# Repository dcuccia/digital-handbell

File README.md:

# Digital Handbell

**A real ringing gesture. A digitally voiced bell. An open design to build together.**

We're developing a rechargeable, motion-triggered musical instrument with a
local speaker, custom electronics, and a removable cartridge inside a
3D-printed bell. The goal is expressive, affordable music-making without a
phone or computer during play.

[Project site and 3D board](https://dcuccia.github.io/digital-handbell/) ·
[Build a handbell](docs/build-a-handbell.md) ·
[Explore the design](docs/design-gallery.md) ·
[Roadmap](docs/roadmap.md) ·
[Join the project](CONTRIBUTING.md) ·
[Documentation](docs/README.md)

*Enclosure concept, not a product photograph. These preserved CAD views
predate the latest six-layer PCB; fitting that board and its speaker
connector into the assembly is still on the roadmap.*

## Where we are

**November 2026: the six-layer PCB has reached zero unconnected items, and
the first prototype PCBA batch has been ordered.** The next step is turning
those boards into a reviewed, working instrument.

| Ready to explore | Still to do |
|---|---|
| Native KiCad schematic, routed PCB and local libraries | Electrical/DFM review and disposition of remaining rule findings |
| FreeCAD enclosure/cartridge studies and inert fit-print files | Updated assembly for the six-layer board, connector/harness clearance and physical fit |
| Prototype PCBA order placed with JLCPCB (quoted as 10 PCBs, 8 assembled) | Incoming inspection: confirm substitutions, via fill, placements and polarity on arrival, then staged bring-up |
| Firmware, audio and gesture requirements | Implement and demonstrate a sounding instrument; measure latency, noise and runtime |

This is **an engineering prototype, not a build-ready kit**. Ordering
first articles is how we find out what works; it is not a fabrication
release or safety approval. Zero opens means the connectivity check found
no unconnected items; it does not prove the circuit works. The public
snapshot retains 291 non-open DRC findings
and 46 schematic-parity findings. Electrical, mechanical, manufacturing
and safety review remain open. No child-use qualification is claimed.

[Board review and remaining risks](docs/pcb-review-2026-11.md) ·
[Order package](hardware/handbell/quote-prep/2026-11-09-six-layer/README.md) ·
[Incoming checks](hardware/handbell/quote-prep/2026-11-09-six-layer/unresolved-before-ordering.md)

## Inside the design

| Subsystem | Current direction |
|---|---|
| Processing | RP2040 with 2 MB QSPI flash; CircuitPython is the planned firmware path |
| Motion | LSM6DSOX six-axis accelerometer/gyroscope for ringing and damping experiments |
| Sound | MAX98357A I2S amplifier, TPS61023 boosted audio rail and a 40 mm speaker |
| Power and service | Rechargeable 1S Li-ion design, cell protection, USB-C charging/programming and debug access |
| Electronics | Six copper layers; 83 fitted parts: 81 front-side electronic parts and two rear battery contacts |
| Enclosure | Original printed shell, black handle and removable speaker/PCB/cell cartridge |

The intended behavior is local and offline: recognize a ringing gesture,
play a bell sound, and stay quiet between notes. Natural damping,
velocity response, note selection and reliable gesture detection are
development goals, not demonstrated features. Wireless is a future option,
not a dependency of the first instrument.

### The ordered PCBA

| Front: electronics | Back: battery clips |
|:---:|:---:|
|  |  |

*KiCad renders of public snapshot `2f738ccb`, not photographs. Package
models and disclosed stand-ins are used; the battery clips and J1 speaker
connector are simplified project proxies. This is not a fit check.*
**[Rotate it in 3D on the project site](https://dcuccia.github.io/digital-handbell/)** ·
[Build a handbell](docs/build-a-handbell.md) ·
[More views](docs/design-gallery.md)

## Explore without getting lost

| I want to... | Start here |
|---|---|
| See the bell and board | [Design gallery](docs/design-gallery.md) or the [3D project site](https://dcuccia.github.io/digital-handbell/) |
| Build one: parts, printing, harness, assembly | [Build a handbell](docs/build-a-handbell.md) |
| Open the latest electronics | [Six-layer review snapshot](hardware/handbell/iterations/printed-bell-six-layer-review/README.md) |
| Open the enclosure or find STEP/STL files | [Mechanical asset guide](mechanical/README.md) |
| Understand what is next | [Roadmap](docs/roadmap.md) |
| Help with a specific part | [Contributing](CONTRIBUTING.md) |
| Understand the circuits and intended behavior | [Architecture](docs/architecture.md) and [firmware/audio plan](docs/firmware-and-audio.md) |
| Find older experiments or engineering evidence | [Documentation index](docs/README.md) and [hardware revision guide](hardware/handbell/iterations/README.md) |

Keep the whole checkout when opening CAD: some library paths reference
sibling directories. KiCad 10.0.6 and FreeCAD 1.1.3 have been exercised.
No CAD installation is needed to browse the gallery or plans.

## Come build with us

There is useful work for software developers, electronics reviewers,
mechanical designers, musicians and curious first-time contributors.
Near-term needs include CircuitPython/audio experiments, motion replay
tools, PCB review, the updated cartridge fit, and clear assembly/test
documentation. You do not need to route a PCB to help.

Pick a workstream in the [contribution guide](CONTRIBUTING.md), or introduce
your idea in an [issue](https://github.com/dcuccia/digital-handbell/issues).
We track work in the [project board](https://github.com/users/dcuccia/projects/1)
and keep decisions and evidence in the repository.

## Open design, with attribution

The electronics adapt published Adafruit designs, including the RP2040
Prop-Maker Feather, LSM6DSOX breakout and TPS61023 MiniBoost. Original
software, documentation and mechanical work use MIT; adapted hardware
retains **CC BY-SA 3.0**. Mixed CAD exports and images retain their
electronics attribution. See [ATTRIBUTION.md](ATTRIBUTION.md) for the
per-asset boundaries; this is not an Adafruit-endorsed product.

The [2023 design notes](Design%20Notes.md) and
[system diagram](System%20Diagram.pptx) remain preserved. The
[research and routing history](docs/README.md#history-and-research)
records how we reached the current design without making every experiment
the starting point for a new contributor.

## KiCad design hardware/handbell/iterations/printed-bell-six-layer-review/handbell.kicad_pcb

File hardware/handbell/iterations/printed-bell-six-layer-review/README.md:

# Printed-bell six-layer zero-open review snapshot

**Current public electronics review target, November 2026.** This is a
provenance-cleared snapshot, not a fabrication, CAD-fit, functional, safety
or child-use release. The older 37-open four-layer board is preserved
separately; do not use it as the current quote source.

[Project home](../../../../README.md) ·
[Review and risks](../../../../docs/pcb-review-2026-11.md) ·
[Gallery](../../../../docs/design-gallery.md) ·
[Revision guide](../README.md)

## Open and inspect

| Artifact | Purpose |
|---|---|
| [handbell.kicad_pro](handbell.kicad_pro) | Open this project in KiCad 10.0.6; retain the whole checkout for libraries |
| [handbell.kicad_sch](handbell.kicad_sch) | Native schematic with embedded symbols |
| [handbell.kicad_pcb](handbell.kicad_pcb) | Six-layer board `2f738ccb`; 104 footprints, 83 fitted parts |
| [MANIFEST.sha256](MANIFEST.sha256) | Packaged source hashes |
| [Native DRC](reports/native-drc.json) | Zero opens, 291 non-open findings, 46 parity findings; not a clean-board claim |
| [Publication validation](reports/publication-validation.json) | Exact source/delta, library and publication checks |
| [Quote package](../../quote-prep/2026-11-09-six-layer/README.md) | Matching BOM/CPL, quote history and remaining order gates |

The [most recent completed mechanical assembly](../../../../mechanical/README.md)
still binds an older board. There is no six-layer fit-qualified assembly
or populated STEP here.

## Source and provenance

The PCB is a publication derivative of private routing milestone
`0051b2e32c78533f102f3e20cb1bdac3c23377ec9d53b594b4ae5deda663a6bd`.
Only J1's footprint expression was replaced. Its copper lands are independently
derived from the JST ACHL dimensional drawing and retain the accepted pose,
pad numbers, nets, and copper geometry. All non-J1 native objects and saved
fills are preserved by exact-complement proof.

The source project retains the harmless historical internal
`meta.filename = routed-c1.kicad_pro`. The schematic is self-contained for
review, but blanket “Update Footprints from Library” is unsupported for three
legacy schematic alias names; do not use that command as a review step.

See `reports/publication-validation.json` for hashes, geometry, DRC results,
dependency checks, privacy checks, and limits.

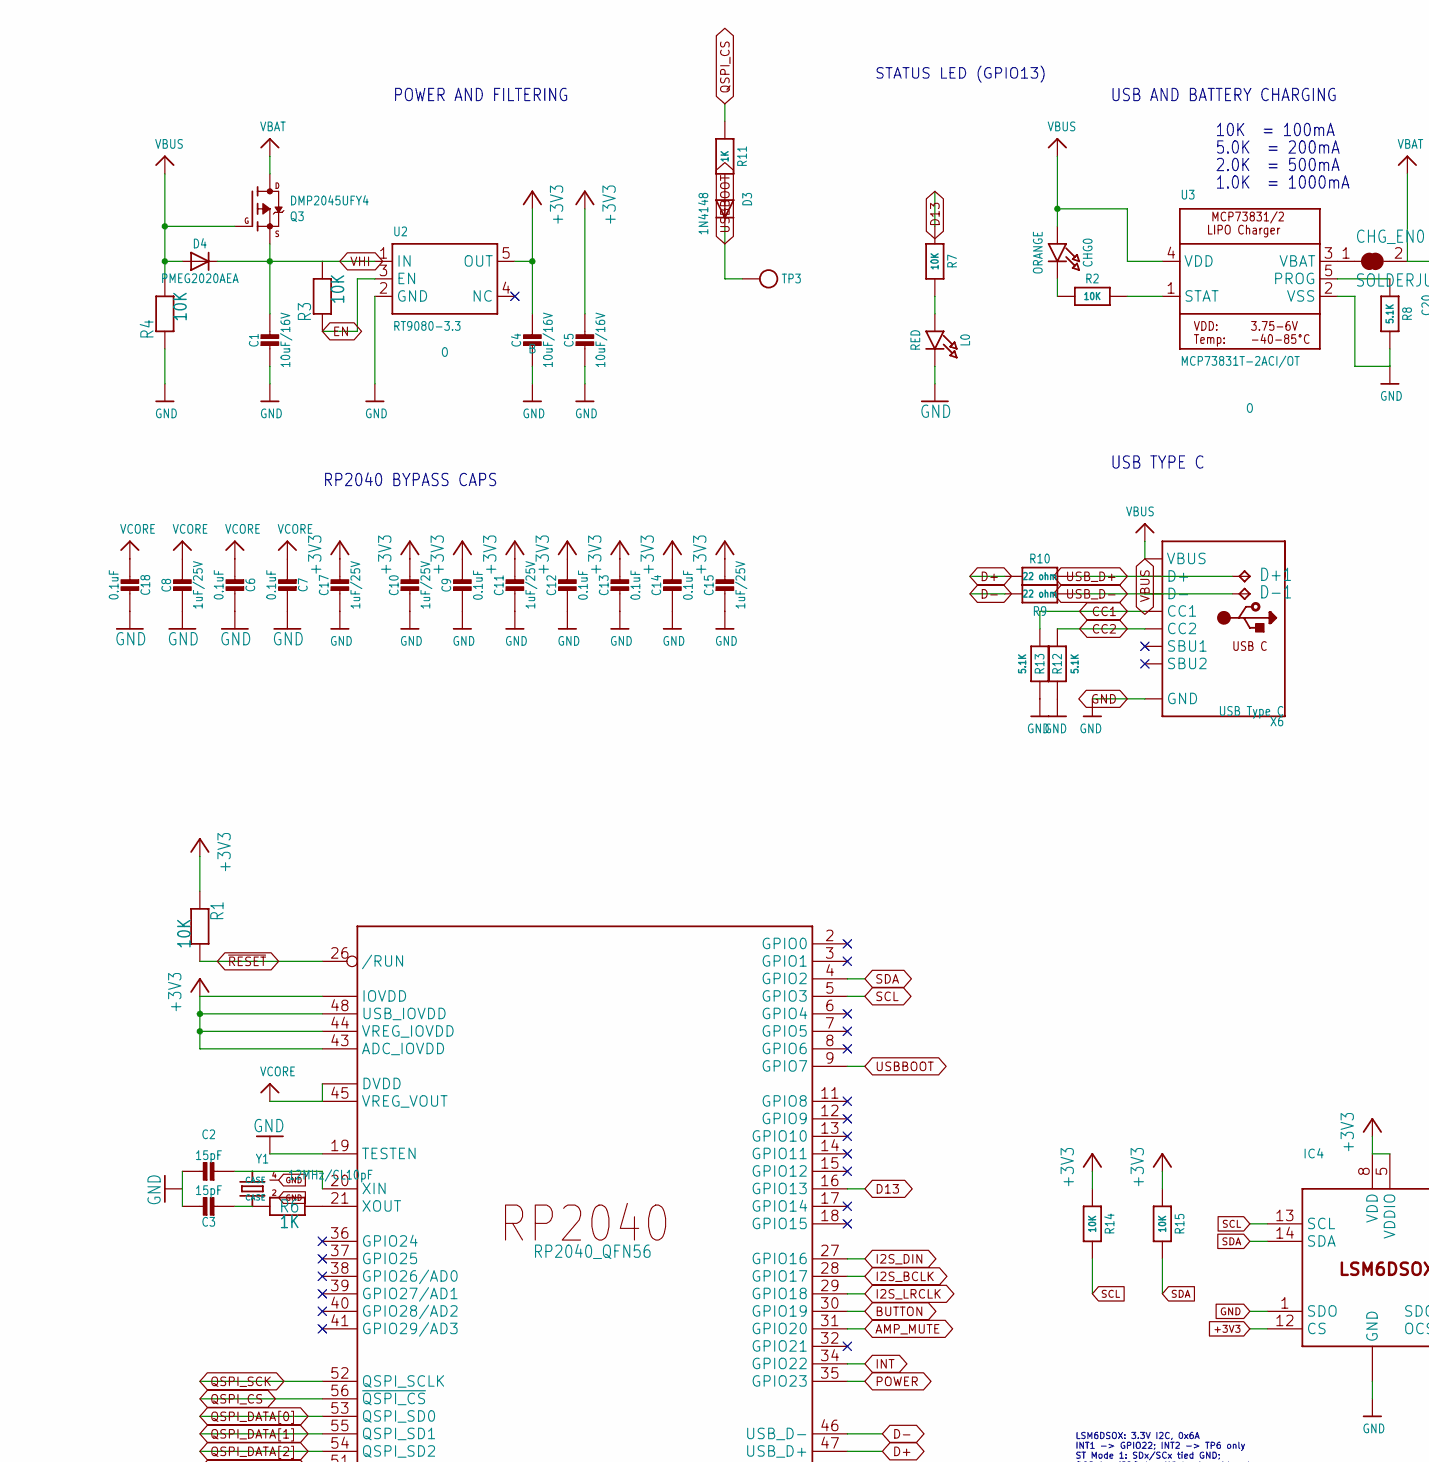
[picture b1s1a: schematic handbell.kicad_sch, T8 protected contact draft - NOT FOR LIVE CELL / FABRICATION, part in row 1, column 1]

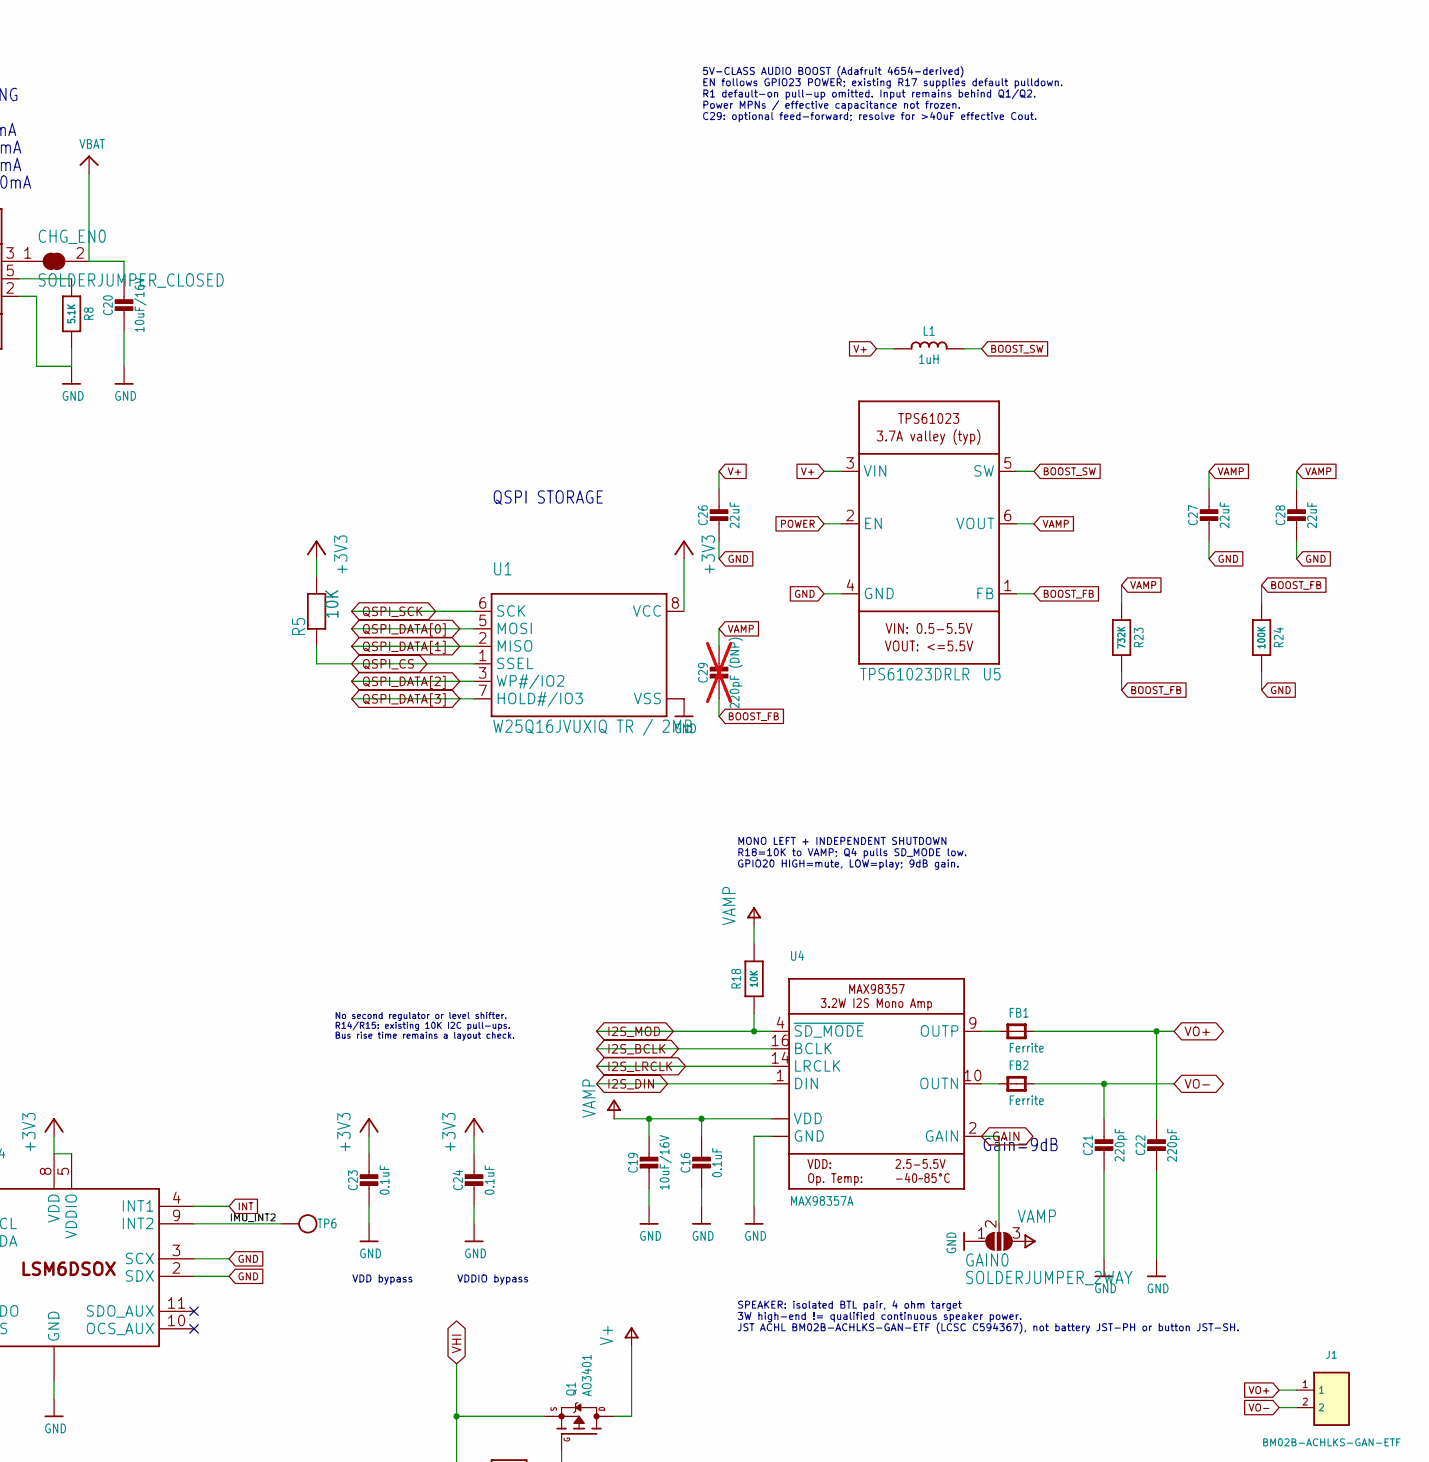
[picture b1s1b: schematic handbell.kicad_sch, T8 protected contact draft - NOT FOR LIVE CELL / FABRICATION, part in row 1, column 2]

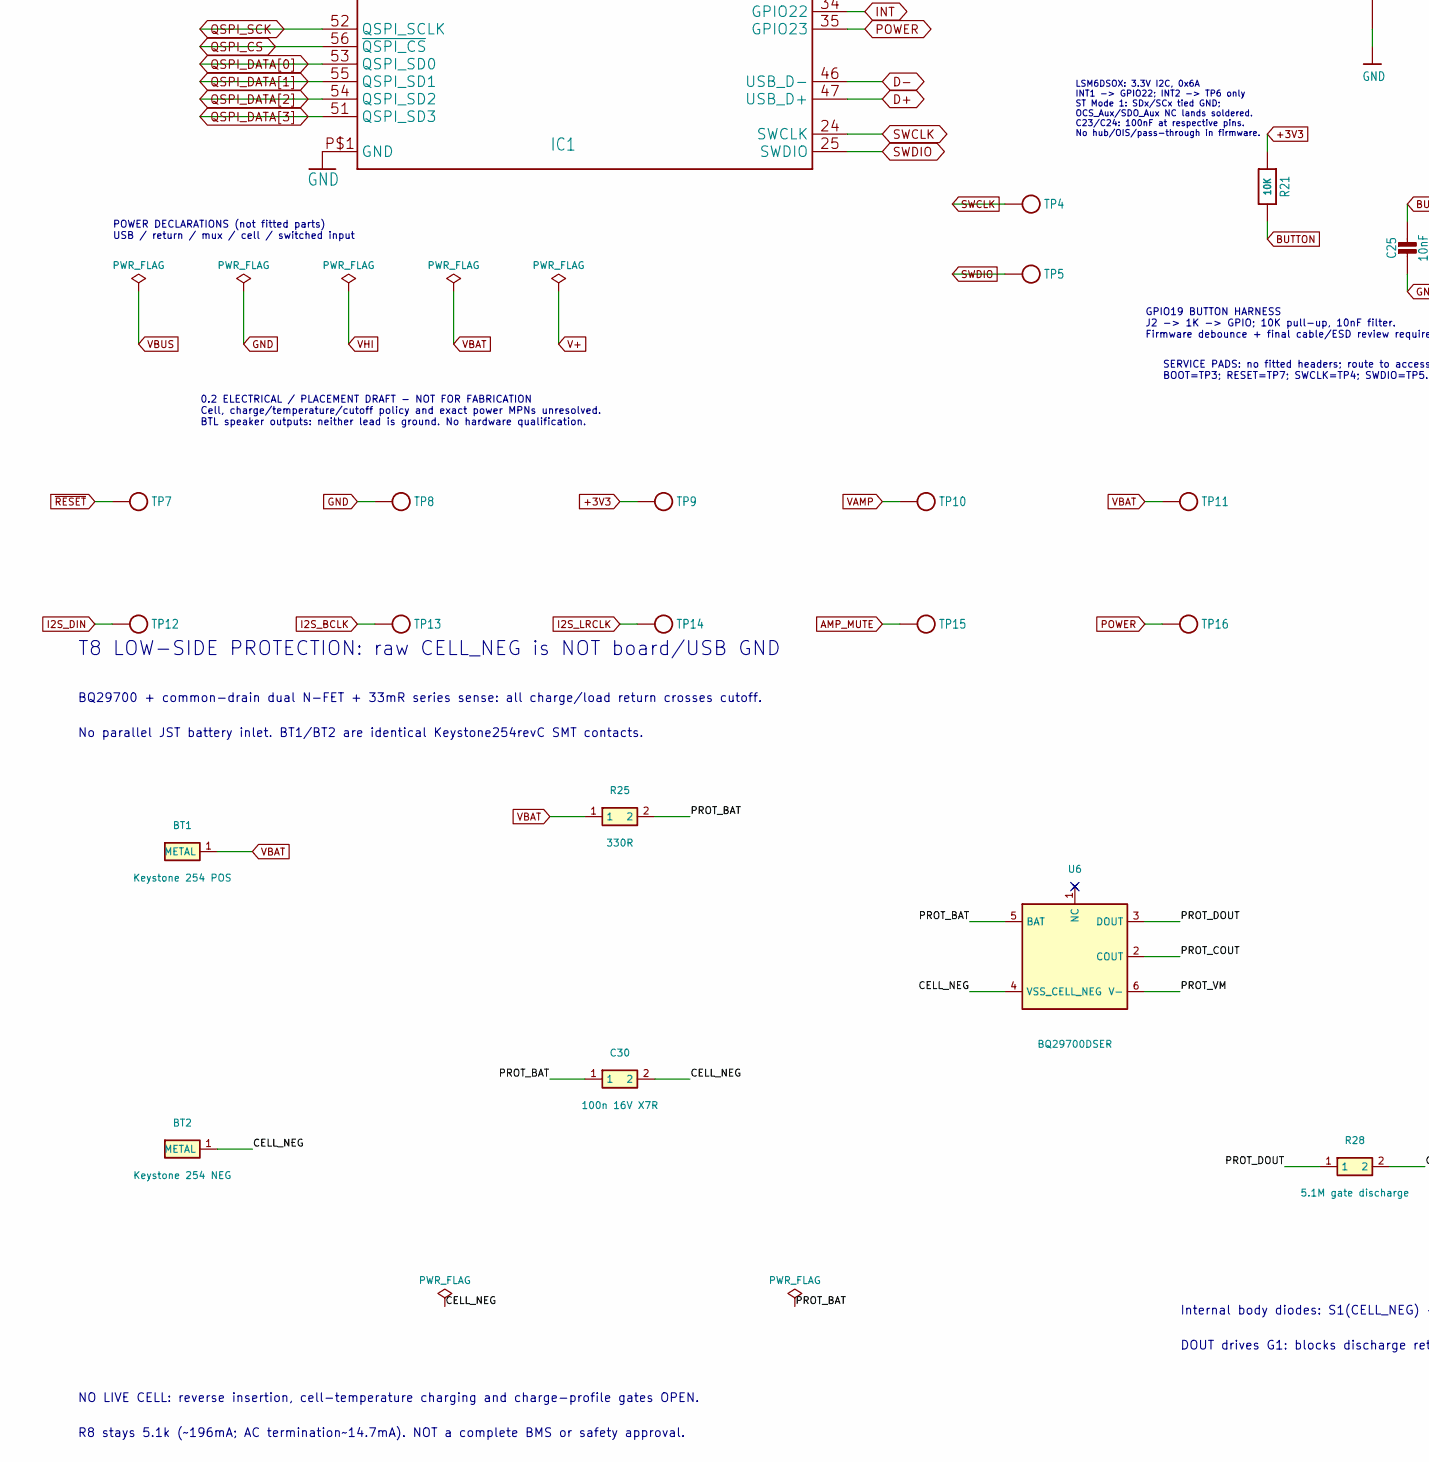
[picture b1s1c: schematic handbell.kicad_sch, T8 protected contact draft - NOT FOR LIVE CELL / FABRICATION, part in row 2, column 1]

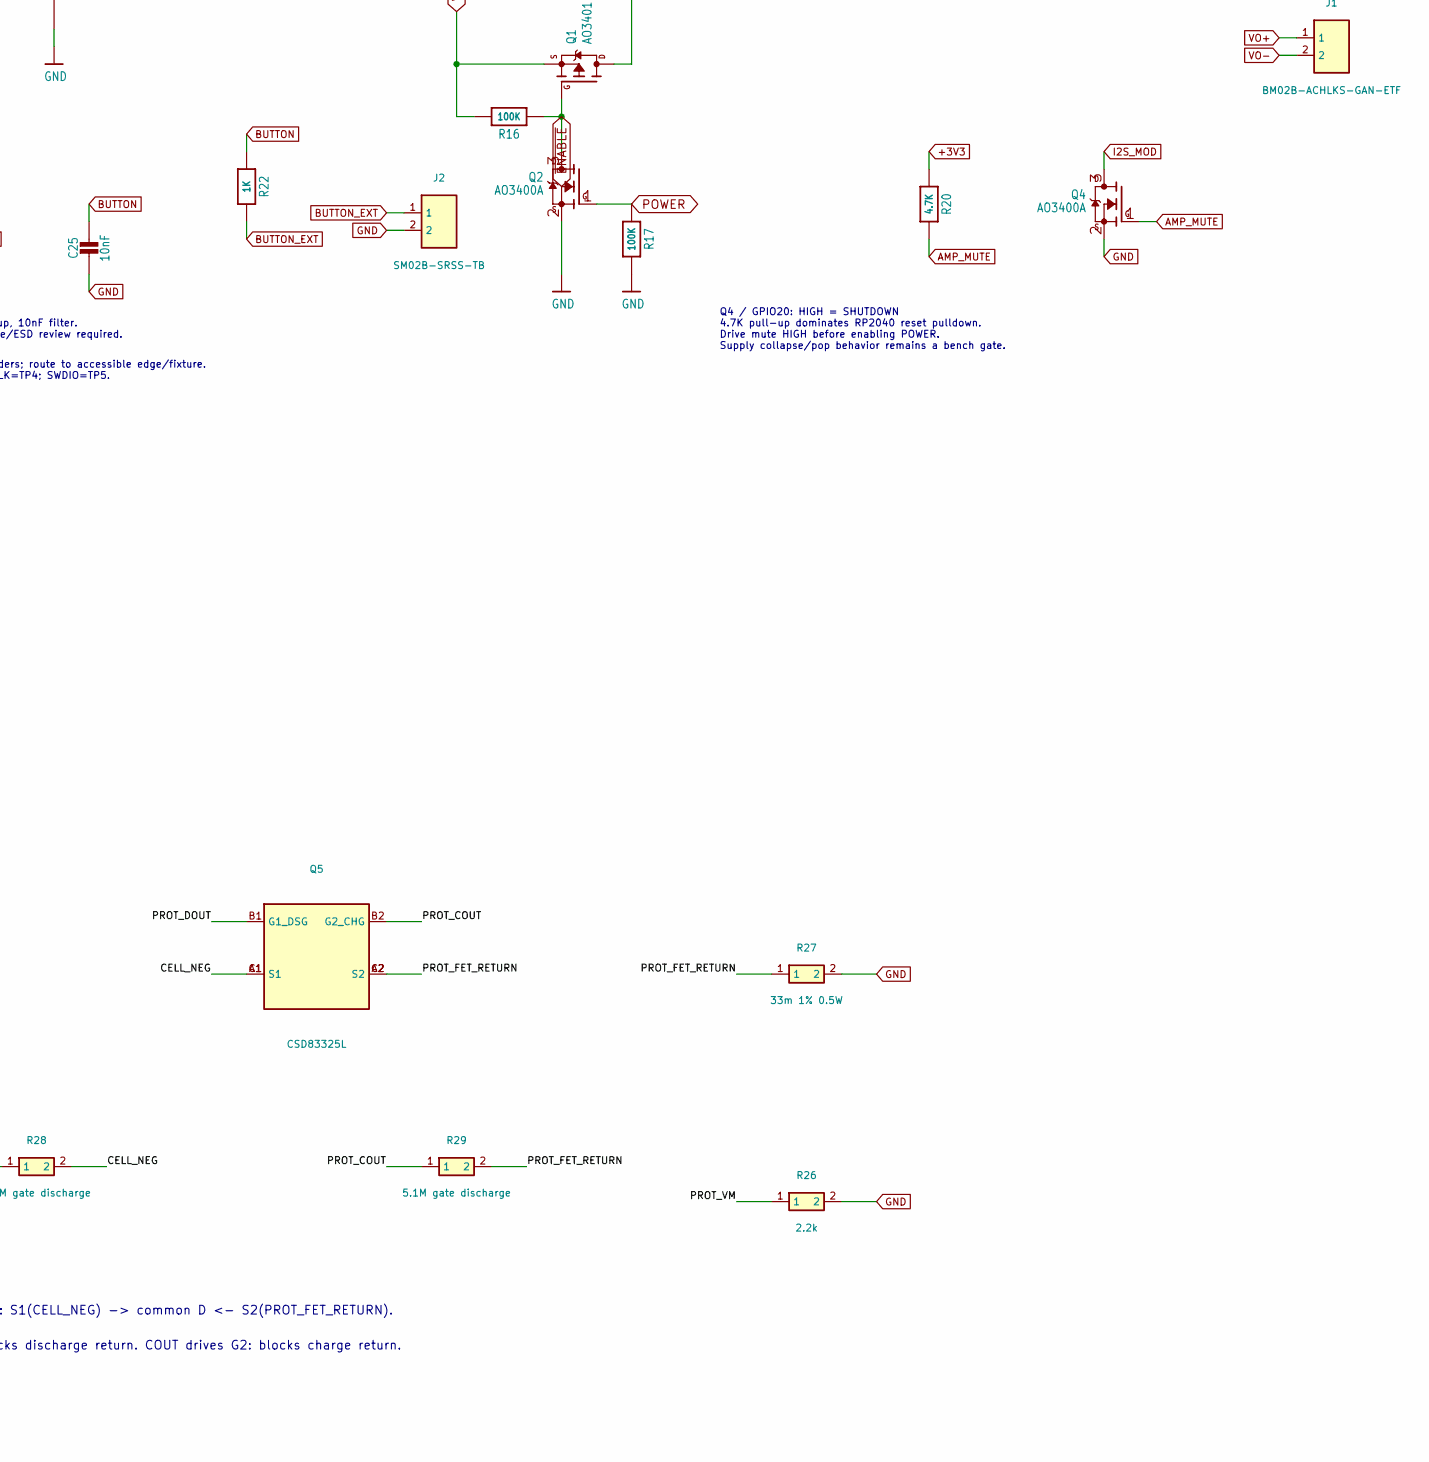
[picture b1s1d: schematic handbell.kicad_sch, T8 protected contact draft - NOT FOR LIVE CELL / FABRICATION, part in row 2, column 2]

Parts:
BT1: Keystone 254 POS; Keystone_254_RevC; MPN 254
BT2: Keystone 254 NEG; Keystone_254_RevC; MPN 254
C1, C4, C5, C19, C20: 10uF/16V; Murata_GRM21_10uF_Reflow; MPN GRM21BR61C106KE15L
C2, C3: 15pF; GRM1555C1H150JA01D; MPN GRM1555C1H150JA01D
C6, C7, C9, C12, C13, C14, C16, C18, C23, C24: 0.1uF; _0402NO; MPN GRM155R71C104KA88D
C8, C10, C11, C15, C17: 1uF/25V; _0402NO; MPN GRM155R61E105KA12D
C21, C22: 220pF; _0402NO; MPN GRM1555C1H221JA01D
C25: 10nF; _0402NO; MPN GRM155R71C103KA01D
C26, C27, C28: 22uF; Murata_GRM21_22uF_Reflow; MPN GRM21BR61C226ME44L
C29: 220pF (DNP); _0402NO; not fitted
C30: 100n 16V X7R; _0402NO; MPN GRM155R71C104KA88D
CHG0: ORANGE; CHIPLED_0603_NOOUTLINE; MPN APT1608LSECK/J4-PRV
CHG_EN0: SOLDERJUMPER_CLOSED; SolderJumper-2_P1.3mm_Bridged_Pad1.0x1.5mm
D3: 1N4148; SOD-323_MINI; MPN 1N4148WS-7-F
D4: PMEG2020AEA; SOD-323F; MPN PMEG2020AEA,115
D+1: TPB1,27; B1,27
D-1: TPB1,27; B1,27
FB1, FB2: Ferrite; Murata_BLM18SG121_WideCopper; MPN BLM18SG121TN1D
GAIN0: SOLDERJUMPER_2WAY; SolderJumper-3_P1.3mm_Open_Pad1.0x1.5mm
IC1: RP2040_QFN56; QFN56_7MM_REDUCEDEPAD; MPN RP2040; LCSC C2040
IC4: LSM6DSOXTR; LGA-14L; MPN LSM6DSOXTR
J1: BM02B-ACHLKS-GAN-ETF; JST_ACHL_BM02B-ACHLKS-GAN-ETF; MPN BM02B-ACHLKS-GAN-ETF
J2: SM02B-SRSS-TB; JST_SH_SM02B-SRSS-TB_1x02-1MP_P1.00mm_Horizontal; MPN SM02B-SRSS-TB
L0: RED; CHIPLED_0603_NOOUTLINE; MPN APT1608LSECK/J3-PRV
L1: 1uH; TDK_VLS5045EX_Reflow; MPN VLS5045EX-1R0N
Q1: AO3401; SOT23-WIDE; MPN AO3401
Q2: AO3400A; SOT23-WIDE; MPN AO3400A
Q3: DMP2045UFY4; DFN2015-3_DrainPad; MPN DMP2045UFY4-7
Q4: AO3400A; SOT-23; MPN AO3400A
Q5: CSD83325L; CSD83325L_YJE6; MPN CSD83325L
R1, R2, R3, R4, R5, R7, R14, R15, R18, R21: 10K; _0402NO; MPN RC0402FR-0710KL
R6, R11, R22: 1K; _0402NO; MPN RC0402FR-071KL
R8, R12, R13: 5.1K; _0402NO; MPN RC0402FR-075K1L
R9, R10: 22 ohm; _0402NO; MPN RC0402FR-0722RL
R16, R17, R24: 100K; _0402NO; MPN RC0402FR-07100KL
R20: 4.7K; _0402NO; MPN RC0402FR-074K7L
R23: 732K; _0402NO; MPN RC0402FR-07732KL
R25: 330R; _0402NO; MPN RC0402FR-07330RL
R26: 2.2k; _0402NO; MPN RC0402FR-072K2L
R27: 33m 1% 0.5W; ERJ6BW_0805_Panasonic_Example; MPN ERJ-6BWFR033V
R28, R29: 5.1M gate discharge; _0402NO; MPN RC0402FR-075M1L
TP3, TP4, TP6: TESTPOINTROUND1.5MMNO; TESTPOINT_ROUND_1.5MM_NO
TP5: TESTPOINTROUND1.5MMNO; TP_BareProbe_D0.3mm
TP7: ~{RESET}; TESTPOINT_ROUND_1.5MM_NO
TP8: GND; TESTPOINT_ROUND_1.5MM_NO
TP9: +3V3; TESTPOINT_ROUND_1.5MM_NO
TP10: VAMP; TESTPOINT_ROUND_1.5MM_NO
TP11: VBAT; TESTPOINT_ROUND_1.5MM_NO
TP12: I2S_DIN; TESTPOINT_ROUND_1.5MM_NO
TP13: I2S_BCLK; TESTPOINT_ROUND_1.5MM_NO
TP14: I2S_LRCLK; TP_BareProbe_D0.6mm
TP15: AMP_MUTE; TESTPOINT_ROUND_1.5MM_NO
TP16: POWER; TESTPOINT_ROUND_1.5MM_NO
U1: W25Q16JVUXIQ TR / 2MB; Winbond_USON8_UX_2x3; MPN W25Q16JVUXIQ TR
U2: RT9080-3.3; SOT23-5; MPN RT9080-33GJ5; JLC_ROTATION 0
U3: MCP73831T-2ACI/OT; SOT23-5; MPN MCP73831T-2ACI/OT; JLC_ROTATION 0
U4: MAX98357A; QFN16_3MM; MPN MAX98357AETE+T
U5: TPS61023DRLR; TPS61023_DRL_TI_Example; MPN TPS61023DRLR
U6: BQ29700DSER; BQ29700_DSE6; MPN BQ29700DSER
X6: USB Type C; USB_C_HRO_TYPE_C_31_M_12_Handbell; MPN TYPE-C-31-M-12; LCSC C165948
Y1: 12MHz/CL10pF; ABM8_272_T3; MPN ABM8-272-T3

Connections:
+3V3: C4.1, C5.1, C9.1, C10.1, C11.1, C12.1, C13.1, C14.1, C15.1, C17.1, C23.1, C24.1, IC1.1 (IOVDD), IC1.10 (IOVDD), IC1.22 (IOVDD), IC1.33 (IOVDD), IC1.42 (IOVDD), IC1.43 (ADC_IOVDD), IC1.44 (VREG_IOVDD), IC1.48 (USB_IOVDD), IC1.49 (IOVDD), IC4.5 (VDDIO), IC4.8 (VDD), IC4.12 (CS), R1.1, R5.2, R14.1, R15.1, R20.1, R21.1, TP9.P$1 (P$1_P$1), U1.8 (VCC), U2.5 (OUT)
/CELL_NEG: BT2.1 (METAL_1), C30.2, Q5.A1 (S1), Q5.C1 (S1), R28.2, U6.4 (VSS_CELL_NEG)
/IMU_INT2: IC4.9 (INT2), TP6.P$1 (P$1_P$1)
/PROT_BAT: C30.1, R25.2, U6.5 (BAT)
/PROT_COUT: Q5.B2 (G2_CHG), R29.1, U6.2 (COUT)
/PROT_DOUT: Q5.B1 (G1_DSG), R28.1, U6.3 (DOUT)
/PROT_FET_RETURN: Q5.A2 (S2), Q5.C2 (S2), R27.1, R29.2
/PROT_VM: R26.1, U6.6 (V-)
AMP_MUTE: IC1.31 (GPIO20), Q4.1 (G), R20.2, TP15.P$1 (P$1_P$1)
BOOST_FB: C29.2, R23.2, R24.1, U5.1 (FB)
BOOST_SW: L1.P$2 (2), U5.5 (SW)
BUTTON: C25.1, IC1.30 (GPIO19), R21.2, R22.1
BUTTON_EXT: J2.1, R22.2
CC1: R13.2, X6.A5 (CC1)
CC2: R12.2, X6.B5 (CC2)
D13: IC1.16 (GPIO13), R7.1
D+: IC1.47 (USB_D+), R10.2
D-: IC1.46 (USB_D-), R9.2
EN: R3.1, U2.3 (EN)
GAIN: GAIN0.2, U4.2 (GAIN)
GND: C1.2, C2.1, C3.1, C4.2, C5.2, C6.1, C7.1, C8.2, C9.2, C10.2, C11.2, C12.2, C13.2, C14.2, C15.2, C16.2, C17.2, C18.1, C19.2, C20.2, C21.2, C22.2, C23.2, C24.2, C25.2, C26.2, C27.2, C28.2, GAIN0.1, IC1.19 (TESTEN), IC1.P$1 (GND), IC4.1 (SDO), IC4.2 (SDX), IC4.3 (SCX), IC4.6 (GND), IC4.7 (GND), J2.2, L0.C, Q2.2 (S), Q4.2 (S), R4.1, R8.2, R12.1, R13.1, R17.2, R24.2, R26.2, R27.2, TP8.P$1 (P$1_P$1), U1.4 (VSS), U1.PAD (VSS), U2.2 (GND), U3.2 (VSS), U4.3 (GND), U4.11 (GND), U4.15 (GND), U4.THERMAL (GND), U5.4 (GND), X6.A1B12 (GND), X6.B1A12 (GND), Y1.2 (CASE), Y1.4 (CASE); also elsewhere on the board
I2S_BCLK: IC1.28 (GPIO17), TP13.P$1 (P$1_P$1), U4.16 (BCLK)
I2S_DIN: IC1.27 (GPIO16), TP12.P$1 (P$1_P$1), U4.1 (DIN)
I2S_LRCLK: IC1.29 (GPIO18), TP14.P$1 (P$1_P$1), U4.14 (LRCLK)
I2S_MOD: Q4.3 (D), R18.1, U4.4 (~SD_MODE)
INT: IC1.34 (GPIO22), IC4.4 (INT1)
unnamed: C3.2, R6.1, Y1.1 (1_1)
unnamed: CHG0.C, R2.1
unnamed: D3.A, R11.2
unnamed: FB1.1, U4.9 (OUTP)
unnamed: FB2.1, U4.10 (OUTN)
unnamed: C2.2, IC1.20 (XIN), Y1.3 (2_3)
unnamed: IC1.21 (XOUT), R6.2
unnamed: L0.A, R7.2
unnamed: R8.1, U3.5 (PROG)
unnamed: R2.2, U3.1 (STAT)
unnamed: CHG_EN0.1, U3.3 (VBAT)
POWER: IC1.35 (GPIO23), Q2.1 (G), R17.1, TP16.P$1 (P$1_P$1), U5.2 (EN)
QSPI_CS: IC1.56 (~QSPI_CS), R5.1, R11.1, U1.1 (SSEL)
QSPI_DATA[0]: IC1.53 (QSPI_SD0), U1.5 (MOSI)
QSPI_DATA[1]: IC1.55 (QSPI_SD1), U1.2 (MISO)
QSPI_DATA[2]: IC1.54 (QSPI_SD2), U1.3 (WP#/IO2)
QSPI_DATA[3]: IC1.51 (QSPI_SD3), U1.7 (HOLD#/IO3)
QSPI_SCK: IC1.52 (QSPI_SCLK), U1.6 (SCK)
SCL: IC1.5 (GPIO3), IC4.13 (SCL), R14.2
SDA: IC1.4 (GPIO2), IC4.14 (SDA), R15.2
SWCLK: IC1.24 (SWCLK), TP4.P$1 (P$1_P$1)
SWDIO: IC1.25 (SWDIO), TP5.P$1 (P$1_P$1)
USBBOOT: D3.C, IC1.9 (GPIO7), TP3.P$1 (P$1_P$1)
USB_D+: D+1.TP (TP_TP), R10.1, X6.A6 (D+), X6.B6 (D+)
USB_D-: D-1.TP (TP_TP), R9.1, X6.A7 (D-), X6.B7 (D-)
V+: C26.1, L1.P$1 (1), Q1.3 (D), U5.3 (VIN)
VAMP: C16.1, C19.1, C27.1, C28.1, C29.1, GAIN0.3, R18.2, R23.1, TP10.P$1 (P$1_P$1), U4.7 (VDD), U4.8 (VDD), U5.6 (VOUT)
VBAT: BT1.1 (METAL_1), C20.1, CHG_EN0.2, Q3.3 (D), R25.1, TP11.P$1 (P$1_P$1)
VBUS: CHG0.A, D4.A, Q3.1 (G), R4.2, U3.4 (VDD), X6.A4B9 (VBUS), X6.B4A9 (VBUS)
VCORE: C6.2, C7.2, C8.1, C18.2, IC1.23 (DVDD), IC1.45 (VREG_VOUT), IC1.50 (DVDD)
VHI: C1.1, D4.C, Q1.2 (S), Q3.2 (S), R3.2, R16.2, U2.1 (IN)
VO+: C22.1, FB1.2, J1.1
VO-: C21.1, FB2.2, J1.2
~ENABLE: Q1.1 (G), Q2.3 (D), R16.1
~RESET: IC1.26 (/RUN), R1.2, TP7.P$1 (P$1_P$1)

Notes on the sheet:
POWER AND FILTERING
MONO LEFT + INDEPENDENT SHUTDOWN R18=10K to VAMP; Q4 pulls SD_MODE low. GPIO20 HIGH=mute, LOW=play; 9dB gain.
USB AND BATTERY CHARGING
Gain=9dB
STATUS LED (GPIO13)
QSPI STORAGE
USB TYPE C
RP2040 BYPASS CAPS
5.0K = 200mA
2.0K = 500mA
10K = 100mA
1.0K = 1000mA
POWER DECLARATIONS (not fitted parts) USB / return / mux / cell / switched input
0.2 ELECTRICAL / PLACEMENT DRAFT - NOT FOR FABRICATION Cell, charge/temperature/cutoff policy and exact power MPNs unresolved. BTL speaker outputs: neither lead is ground. No hardware qualification.
VDD bypass
VDDIO bypass
LSM6DSOX: 3.3V I2C, 0x6A INT1 -> GPIO22; INT2 -> TP6 only ST Mode 1: SDx/SCx tied GND; OCS_Aux/SDO_Aux NC lands soldered. C23/C24: 100nF at respective pins. No hub/OIS/pass-through in firmware.
No second regulator or level shifter. R14/R15: existing 10K I2C pull-ups. Bus rise time remains a layout check.
5V-CLASS AUDIO BOOST (Adafruit 4654-derived) EN follows GPIO23 POWER; existing R17 supplies default pulldown. R1 default-on pull-up omitted. Input remains behind Q1/Q2. Power MPNs / effective capacitance not frozen. C29: optional feed-forward; resolve for >40uF effective Cout.
GPIO19 BUTTON HARNESS J2 -> 1K -> GPIO; 10K pull-up, 10nF filter. Firmware debounce + final cable/ESD review required.
Q4 / GPIO20: HIGH = SHUTDOWN 4.7K pull-up dominates RP2040 reset pulldown. Drive mute HIGH before enabling POWER. Supply collapse/pop behavior remains a bench gate.
SPEAKER: isolated BTL pair, 4 ohm target 3W high-end != qualified continuous speaker power. JST ACHL BM02B-ACHLKS-GAN-ETF (LCSC C594367), not battery JST-PH or button JST-SH.
SERVICE PADS: no fitted headers; route to accessible edge/fixture. BOOT=TP3; RESET=TP7; SWCLK=TP4; SWDIO=TP5.
T8 LOW-SIDE PROTECTION: raw CELL_NEG is NOT board/USB GND
BQ29700 + common-drain dual N-FET + 33mR series sense: all charge/load return crosses cutoff.
No parallel JST battery inlet. BT1/BT2 are identical Keystone254revC SMT contacts.
Internal body diodes: S1(CELL_NEG) -> common D <- S2(PROT_FET_RETURN).
DOUT drives G1: blocks discharge return. COUT drives G2: blocks charge return.
NO LIVE CELL: reverse insertion, cell-temperature charging and charge-profile gates OPEN.
R8 stays 5.1k (~196mA; AC termination~14.7mA). NOT a complete BMS or safety approval.

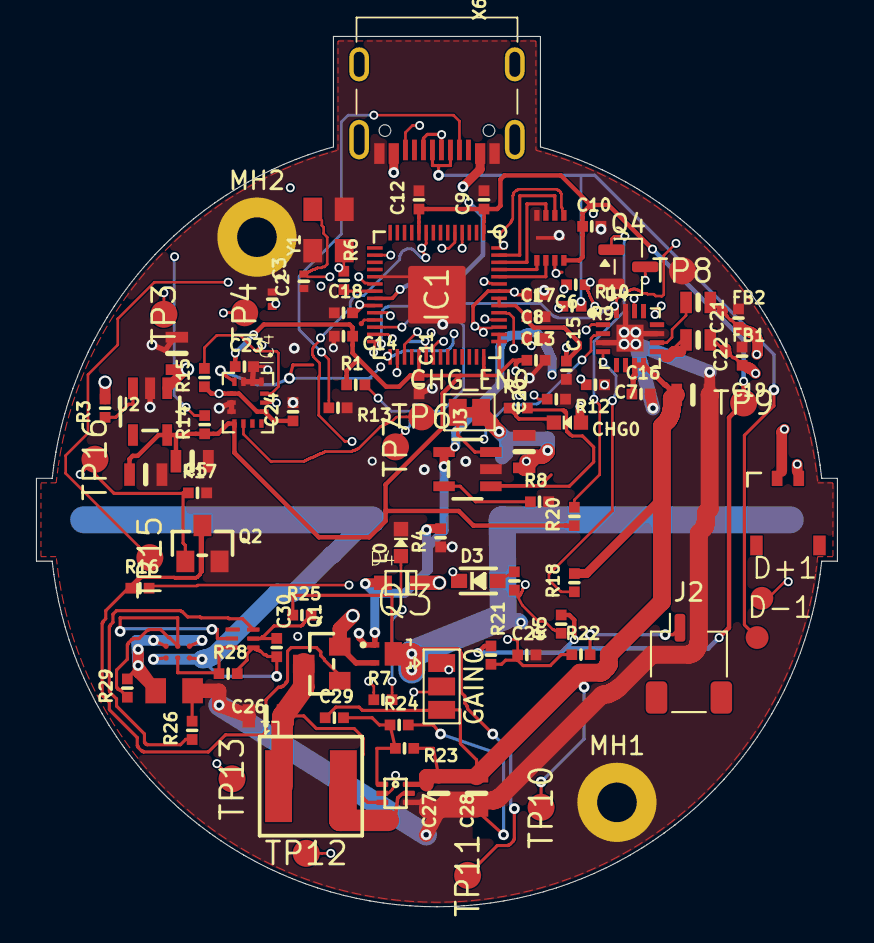
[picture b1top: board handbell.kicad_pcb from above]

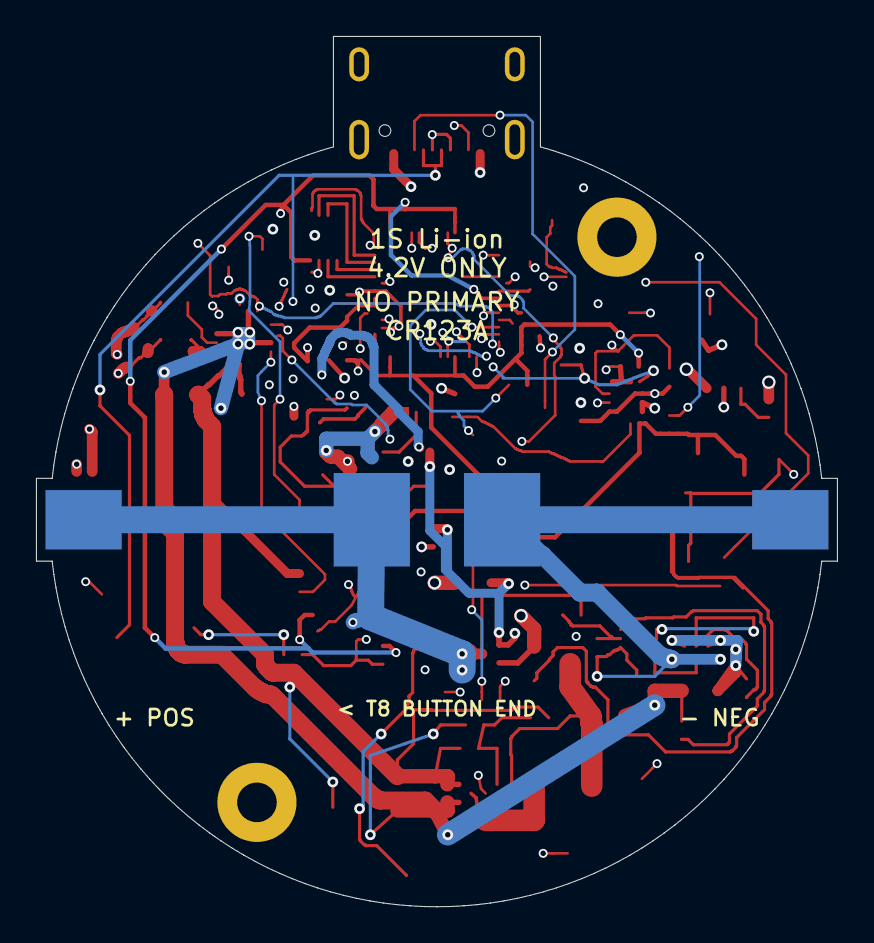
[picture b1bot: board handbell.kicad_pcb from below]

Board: 6 copper layers, 44.5 x 48.3 mm, 104 parts (3 on the bottom side), 61 nets.

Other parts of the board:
MH1, MH2: M2 GND mounting hole; MountingHole_2.2mm_M2_Pad

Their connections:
GND: MH1.1, MH2.1; also elsewhere on the board

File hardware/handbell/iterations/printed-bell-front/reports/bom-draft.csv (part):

Reference,Value,MPN,Footprint,Face,Population,Assembly_note
BT1,Keystone 254 POS,254,T8:Keystone_254_RevC,B,fitted,B-side SMT attachment operation; process/retention not qualified
BT2,Keystone 254 NEG,254,T8:Keystone_254_RevC,B,fitted,B-side SMT attachment operation; process/retention not qualified
C1,10uF/16V,,Adafruit Feather RP2040 Prop-Maker-import-fps:0805-NO,F,fitted,MPN/assembly qualification remains open
C2,22pF,,Adafruit Feather RP2040 Prop-Maker-import-fps:_0402NO,F,fitted,MPN/assembly qualification remains open
C3,22pF,,Adafruit Feather RP2040 Prop-Maker-import-fps:_0402NO,F,fitted,MPN/assembly qualification remains open
C4,10uF/16V,,Adafruit Feather RP2040 Prop-Maker-import-fps:0805-NO,F,fitted,MPN/assembly qualification remains open
C5,10uF/16V,,Adafruit Feather RP2040 Prop-Maker-import-fps:0805-NO,F,fitted,MPN/assembly qualification remains open
C6,0.1uF,,Adafruit Feather RP2040 Prop-Maker-import-fps:_0402NO,F,fitted,MPN/assembly qualification remains open
C7,0.1uF,,Adafruit Feather RP2040 Prop-Maker-import-fps:_0402NO,F,fitted,MPN/assembly qualification remains open
C8,1uF/25V,,Adafruit Feather RP2040 Prop-Maker-import-fps:_0402NO,F,fitted,MPN/assembly qualification remains open
C9,0.1uF,,Adafruit Feather RP2040 Prop-Maker-import-fps:_0402NO,F,fitted,MPN/assembly qualification remains open
C10,1uF/25V,,Adafruit Feather RP2040 Prop-Maker-import-fps:_0402NO,F,fitted,MPN/assembly qualification remains open
C11,1uF/25V,,Adafruit Feather RP2040 Prop-Maker-import-fps:_0402NO,F,fitted,MPN/assembly qualification remains open
C12,0.1uF,,Adafruit Feather RP2040 Prop-Maker-import-fps:_0402NO,F,fitted,MPN/assembly qualification remains open
C13,0.1uF,,Adafruit Feather RP2040 Prop-Maker-import-fps:_0402NO,F,fitted,MPN/assembly qualification remains open
C14,0.1uF,,Adafruit Feather RP2040 Prop-Maker-import-fps:_0402NO,F,fitted,MPN/assembly qualification remains open
C15,1uF/25V,,Adafruit Feather RP2040 Prop-Maker-import-fps:_0402NO,F,fitted,MPN/assembly qualification remains open
C16,0.1uF,,Adafruit Feather RP2040 Prop-Maker-import-fps:_0402NO,F,fitted,MPN/assembly qualification remains open
C17,1uF/25V,,Adafruit Feather RP2040 Prop-Maker-import-fps:_0402NO,F,fitted,MPN/assembly qualification remains open
C18,0.1uF,,Adafruit Feather RP2040 Prop-Maker-import-fps:_0402NO,F,fitted,MPN/assembly qualification remains open
C19,10uF/16V,,Adafruit Feather RP2040 Prop-Maker-import-fps:0805-NO,F,fitted,MPN/assembly qualification remains open
C20,10uF/16V,,Adafruit Feather RP2040 Prop-Maker-import-fps:0805-NO,F,fitted,MPN/assembly qualification remains open
C21,220pF,,Adafruit Feather RP2040 Prop-Maker-import-fps:_0402NO,F,fitted,MPN/assembly qualification remains open
C22,220pF,,Adafruit Feather RP2040 Prop-Maker-import-fps:_0402NO,F,fitted,MPN/assembly qualification remains open
C23,0.1uF,,Adafruit Feather RP2040 Prop-Maker-import-fps:_0402NO,F,fitted,MPN/assembly qualification remains open
C24,0.1uF,,Adafruit Feather RP2040 Prop-Maker-import-fps:_0402NO,F,fitted,MPN/assembly qualification remains open
C25,10nF,,Adafruit Feather RP2040 Prop-Maker-import-fps:_0402NO,F,fitted,MPN/assembly qualification remains open
C26,22uF,,Adafruit Feather RP2040 Prop-Maker-import-fps:0805-NO,F,fitted,MPN/assembly qualification remains open
C27,22uF,,Adafruit Feather RP2040 Prop-Maker-import-fps:0805-NO,F,fitted,MPN/assembly qualification remains open
C28,22uF,,Adafruit Feather RP2040 Prop-Maker-import-fps:0805-NO,F,fitted,MPN/assembly qualification remains open
C29,220pF (DNP),,Adafruit Feather RP2040 Prop-Maker-import-fps:_0402NO,F,DNP,MPN/assembly qualification remains open
C30,100n 16V X7R,GRM155R71C104KA88D,Adafruit Feather RP2040 Prop-Maker-import-fps:_0402NO,F,fitted,Not an order authorization
CHG0,ORANGE,,Adafruit Feather RP2040 Prop-Maker-import-fps:CHIPLED_0603_NOOUTLINE,F,fitted,MPN/assembly qualification remains open
CHG_EN0,SOLDERJUMPER_CLOSED,,Jumper:SolderJumper-2_P1.3mm_Bridged_Pad1.0x1.5mm,F,copper-only,MPN/assembly qualification remains open
D+1,"TPB1,27",,"Adafruit Feather RP2040 Prop-Maker-import-fps:B1,27",F,copper-only,MPN/assembly qualification remains open
D-1,"TPB1,27",,"Adafruit Feather RP2040 Prop-Maker-import-fps:B1,27",F,copper-only,MPN/assembly qualification remains open
D3,1N4148,,Adafruit Feather RP2040 Prop-Maker-import-fps:SOD-323_MINI,F,fitted,MPN/assembly qualification remains open
D4,PMEG2020AEA,,Adafruit Feather RP2040 Prop-Maker-import-fps:SOD-323F,F,fitted,MPN/assembly qualification remains open
FB1,Ferrite,,Adafruit Feather RP2040 Prop-Maker-import-fps:0603-NO,F,fitted,MPN/assembly qualification remains open
FB2,Ferrite,,Adafruit Feather RP2040 Prop-Maker-import-fps:0603-NO,F,fitted,MPN/assembly qualification remains open
GAIN0,SOLDERJUMPER_2WAY,,Jumper:SolderJumper-3_P1.3mm_Open_Pad1.0x1.5mm,F,copper-only,MPN/assembly qualification remains open
IC1,RP2040_QFN56,,Adafruit Feather RP2040 Prop-Maker-import-fps:QFN56_7MM_REDUCEDEPAD,F,fitted,MPN/assembly qualification remains open
IC4,LSM6DSOXTR,,Adafruit_LSM6DSOX-import-fps:LGA-14L,F,fitted,MPN/assembly qualification remains open
J1,504050-0291,504050-0291,Connector_Molex:Molex_Pico-Lock_504050-0291_1x02-1MP_P1.50mm_Horizontal,F,fitted,Not an order authorization
J2,SM02B-SRSS-TB,SM02B-SRSS-TB,Connector_JST:JST_SH_SM02B-SRSS-TB_1x02-1MP_P1.00mm_Horizontal,F,fitted,Not an order authorization
L0,RED,,Adafruit Feather RP2040 Prop-Maker-import-fps:CHIPLED_0603_NOOUTLINE,F,fitted,MPN/assembly qualification remains open
L1,1uH (MPN pending),,Adafruit TPS61023-import-fps:INDUCTOR_5X5MM_TDK_VLC5045,F,fitted,MPN/assembly qualification remains open
Q1,AO3401,,Adafruit Feather RP2040 Prop-Maker-import-fps:SOT23-WIDE,F,fitted,MPN/assembly qualification remains open
Q2,C20917,,Adafruit Feather RP2040 Prop-Maker-import-fps:SOT23-WIDE,F,fitted,MPN/assembly qualification remains open
Q3,DMG3415UFY,,Handbell:DFN2015-3_DrainPad,F,fitted,MPN/assembly qualification remains open
Q4,AO3400A,AO3400A,Package_TO_SOT_SMD:SOT-23,F,fitted,Not an order authorization
Q5,CSD83325L,CSD83325L,T8:CSD83325L_YJE6,F,fitted,Not an order authorization
R1,10K,,Adafruit Feather RP2040 Prop-Maker-import-fps:_0402NO,F,fitted,MPN/assembly qualification remains open
R2,10K,,Adafruit Feather RP2040 Prop-Maker-import-fps:_0402NO,F,fitted,MPN/assembly qualification remains open
R3,10K,,Adafruit Feather RP2040 Prop-Maker-import-fps:_0402NO,F,fitted,MPN/assembly qualification remains open
R4,10K,,Adafruit Feather RP2040 Prop-Maker-import-fps:_0402NO,F,fitted,MPN/assembly qualification remains open
R5,10K,,Adafruit Feather RP2040 Prop-Maker-import-fps:_0402NO,F,fitted,MPN/assembly qualification remains open
R6,1K,,Adafruit Feather RP2040 Prop-Maker-import-fps:_0402NO,F,fitted,MPN/assembly qualification remains open
R7,10K,,Adafruit Feather RP2040 Prop-Maker-import-fps:_0402NO,F,fitted,MPN/assembly qualification remains open
R8,5.1K,,Adafruit Feather RP2040 Prop-Maker-import-fps:_0402NO,F,fitted,MPN/assembly qualification remains open
R9,22 ohm,,Adafruit Feather RP2040 Prop-Maker-import-fps:_0402NO,F,fitted,MPN/assembly qualification remains open
R10,22 ohm,,Adafruit Feather RP2040 Prop-Maker-import-fps:_0402NO,F,fitted,MPN/assembly qualification remains open
R11,1K,,Adafruit Feather RP2040 Prop-Maker-import-fps:_0402NO,F,fitted,MPN/assembly qualification remains open
R12,5.1K,,Adafruit Feather RP2040 Prop-Maker-import-fps:_0402NO,F,fitted,MPN/assembly qualification remains open
R13,5.1K,,Adafruit Feather RP2040 Prop-Maker-import-fps:_0402NO,F,fitted,MPN/assembly qualification remains open
R14,10K,,Adafruit Feather RP2040 Prop-Maker-import-fps:_0402NO,F,fitted,MPN/assembly qualification remains open
R15,10K,,Adafruit Feather RP2040 Prop-Maker-import-fps:_0402NO,F,fitted,MPN/assembly qualification remains open
R16,100K,,Adafruit Feather RP2040 Prop-Maker-import-fps:_0402NO,F,fitted,MPN/assembly qualification remains open
R17,100K,,Adafruit Feather RP2040 Prop-Maker-import-fps:_0402NO,F,fitted,MPN/assembly qualification remains open
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

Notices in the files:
tools/check_handbell.py:
SPDX-License-Identifier: MIT
hardware/handbell/handbell.kicad_sch:
Adapted from Adafruit 5768 / 4438 / 4654; CC BY-SA 3.0. See ATTRIBUTION.md.
hardware/handbell/iterations/printed-bell-six-layer-review/handbell.kicad_pcb:
Adafruit-derived CC BY-SA3.0; not fabrication approval
